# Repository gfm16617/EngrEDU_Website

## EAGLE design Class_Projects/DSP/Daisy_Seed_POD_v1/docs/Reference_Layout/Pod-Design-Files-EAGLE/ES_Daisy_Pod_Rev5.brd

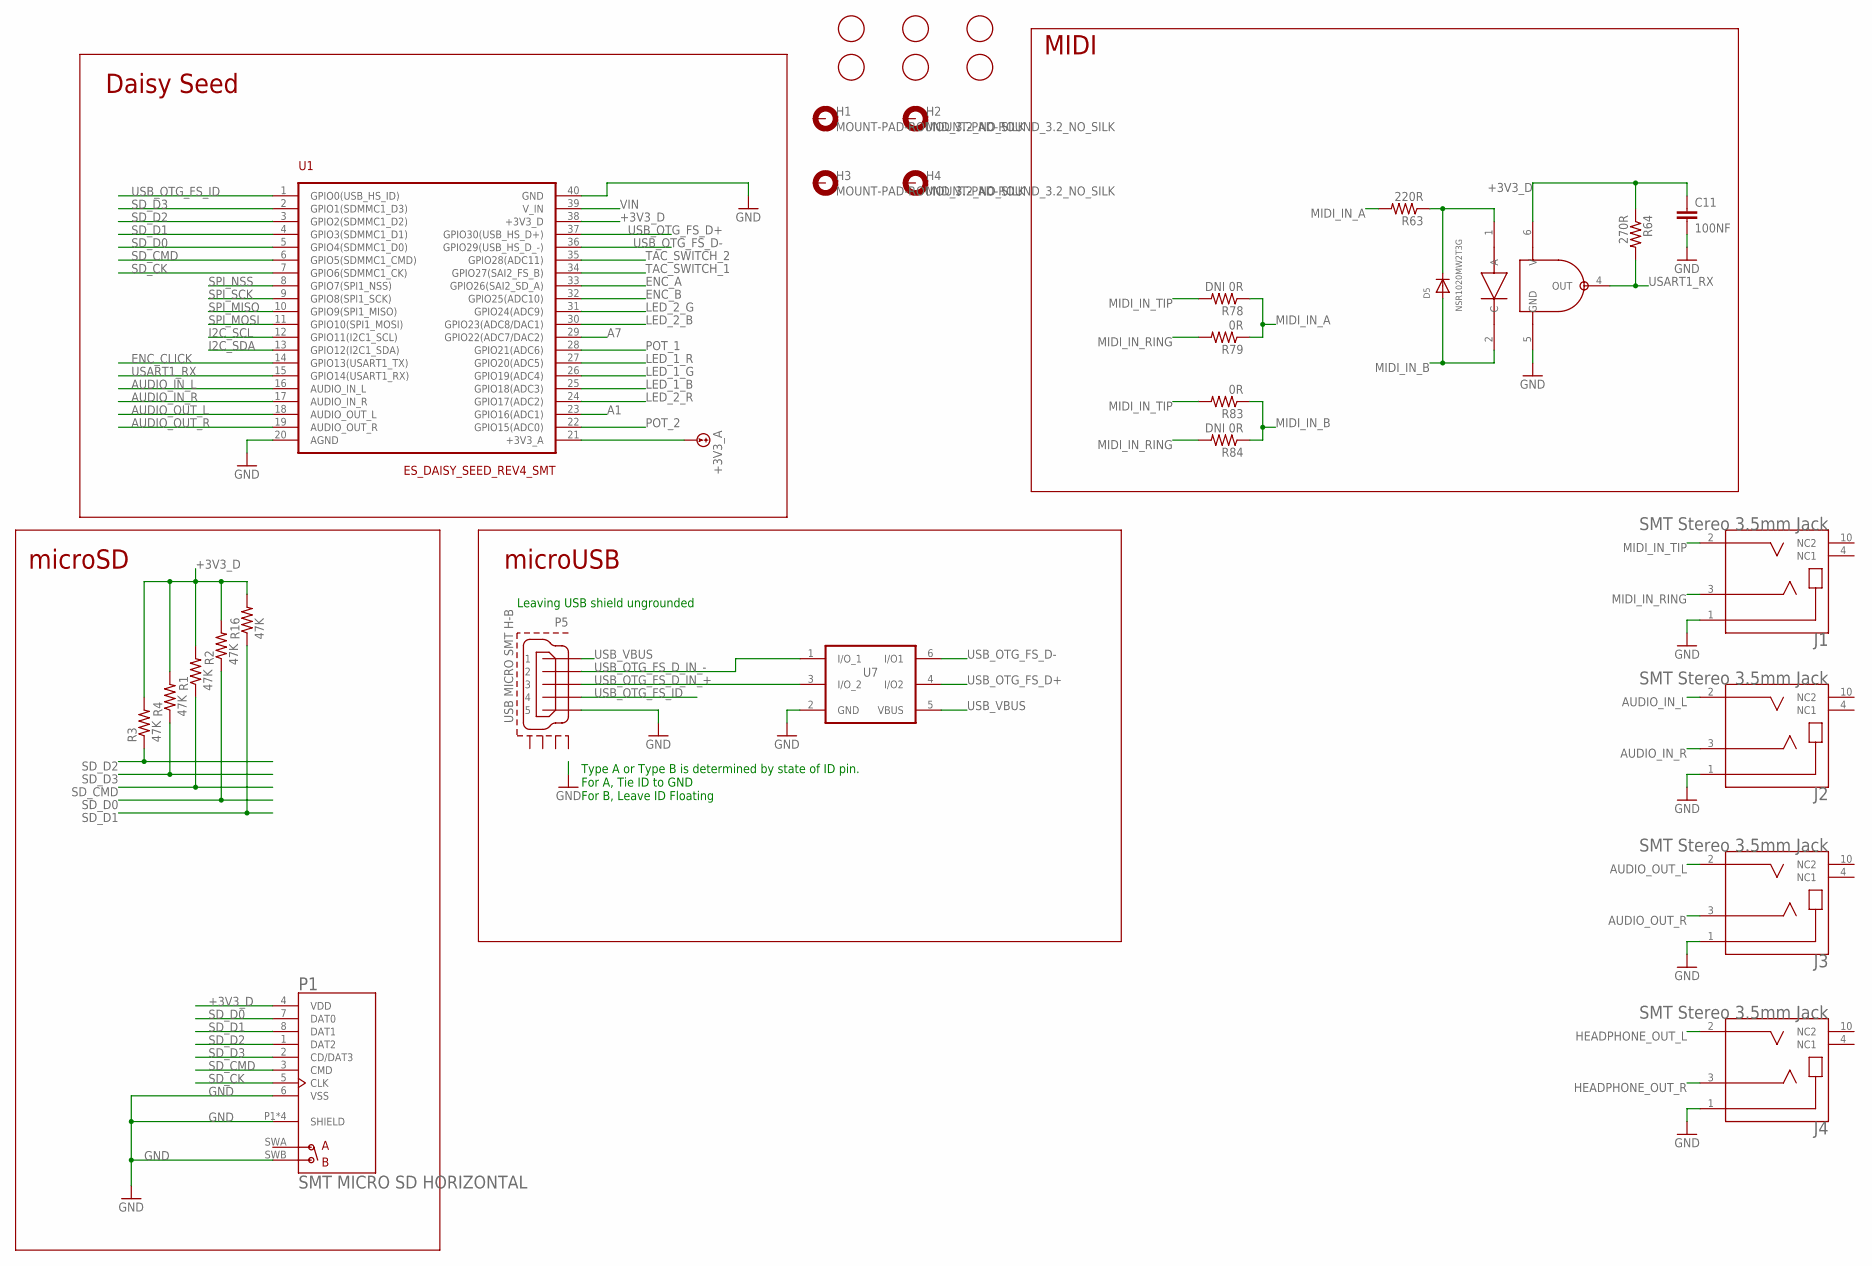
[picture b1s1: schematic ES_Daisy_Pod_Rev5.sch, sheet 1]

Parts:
C11: 100NF; C0402
D5: NSR1020MW2T3G; SOD-323F
FD1, FD2, FD3, FD4, FD5, FD6: FIDUCIAL; FIDUCIAL_1MM
H1, H2, H3, H4: MOUNT-PAD-ROUND_3.2_NO_SILK; 32-PAD_NO_SILK
J1, J2, J3, J4: SMT Stereo 3.5mm Jack; CUI_SJ2-35863B1-SMT-TR
P1: SMT MICRO SD HORIZONTAL; HRS_DM3AT-SF-PEJM5
P5: USB MICRO SMT H-B; 47589-0001_CUT2
R1, R2, R3, R4, R16: 47K; R0603
R63: 220R; R0603
R64: 270R; R0603
R78, R84: DNI 0R; R0603
R79, R83: 0R; R0603
U1: ES_DAISY_SEED_REV4_SMT; ES_DAISY_SEED_SMT
U7: USBLC6 TVS SOT-23-6; SOT-23-6L
U15: H11L1SR2M; DIL06_GULLWING

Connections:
+3V3_A: U1.21 (+3V3_A); also elsewhere on the board
+3V3_D: C11.1, P1.4 (VDD), R1.2, R2.2, R3.2, R4.2, R16.2, R64.1, U1.38 (+3V3_D), U15.6 (V); also elsewhere on the board
A1: U1.23 (GPIO16(ADC1)); also elsewhere on the board
A7: U1.29 (GPIO22(ADC7/DAC2)); also elsewhere on the board
AUDIO_IN_L: J2.2 (TIP), U1.16 (AUDIO_IN_L)
AUDIO_IN_R: J2.3 (RING), U1.17 (AUDIO_IN_R)
AUDIO_OUT_L: J3.2 (TIP), U1.18 (AUDIO_OUT_L); also elsewhere on the board
AUDIO_OUT_R: J3.3 (RING), U1.19 (AUDIO_OUT_R); also elsewhere on the board
ENC_A: U1.33 (GPIO26(SAI2_SD_A)); also elsewhere on the board
ENC_B: U1.32 (GPIO25(ADC10)); also elsewhere on the board
ENC_CLICK: U1.14 (GPIO13(USART1_TX)); also elsewhere on the board
GND: C11.2, J1.1 (SLEEVE), J2.1 (SLEEVE), J3.1 (SLEEVE), J4.1 (SLEEVE), P1.6 (VSS), P1.P1 (SHIELD), P1.P2 (SHIELD), P1.P3 (SHIELD), P1.P4 (SHIELD), P1.SWB (B), P5.5, U1.20 (AGND), U1.40 (GND), U7.2 (GND), U15.5 (GND); also elsewhere on the board
HEADPHONE_OUT_L: J4.2 (TIP); also elsewhere on the board
HEADPHONE_OUT_R: J4.3 (RING); also elsewhere on the board
I2C_SCL: U1.12 (GPIO11(I2C1_SCL)); also elsewhere on the board
I2C_SDA: U1.13 (GPIO12(I2C1_SDA)); also elsewhere on the board
LED_1_B: U1.25 (GPIO18(ADC3)); also elsewhere on the board
LED_1_G: U1.26 (GPIO19(ADC4)); also elsewhere on the board
LED_1_R: U1.27 (GPIO20(ADC5)); also elsewhere on the board
LED_2_B: U1.30 (GPIO23(ADC8/DAC1)); also elsewhere on the board
LED_2_G: U1.31 (GPIO24(ADC9)); also elsewhere on the board
LED_2_R: U1.24 (GPIO17(ADC2)); also elsewhere on the board
MIDI_IN_A: R63.2, R78.1, R79.1
MIDI_IN_B: D5.A, R83.1, R84.1, U15.2 (C)
MIDI_IN_RING: J1.3 (RING), R79.2, R84.2
MIDI_IN_TIP: J1.2 (TIP), R78.2, R83.2
unnamed: D5.C, R63.1, U15.1 (A)
POT_1: U1.28 (GPIO21(ADC6)); also elsewhere on the board
POT_2: U1.22 (GPIO15(ADC0)); also elsewhere on the board
SD_CK: P1.5 (CLK), U1.7 (GPIO6(SDMMC1_CK))
SD_CMD: P1.3 (CMD), R1.1, U1.6 (GPIO5(SDMMC1_CMD))
SD_D0: P1.7 (DAT0), R2.1, U1.5 (GPIO4(SDMMC1_D0))
SD_D1: P1.8 (DAT1), R16.1, U1.4 (GPIO3(SDMMC1_D1))
SD_D2: P1.1 (DAT2), R3.1, U1.3 (GPIO2(SDMMC1_D2))
SD_D3: P1.2 (CD/DAT3), R4.1, U1.2 (GPIO1(SDMMC1_D3))
SPI_MISO: U1.10 (GPIO9(SPI1_MISO)); also elsewhere on the board
SPI_MOSI: U1.11 (GPIO10(SPI1_MOSI)); also elsewhere on the board
SPI_NSS: U1.8 (GPIO7(SPI1_NSS)); also elsewhere on the board
SPI_SCK: U1.9 (GPIO8(SPI1_SCK)); also elsewhere on the board
TAC_SWITCH_1: U1.34 (GPIO27(SAI2_FS_B)); also elsewhere on the board
TAC_SWITCH_2: U1.35 (GPIO28(ADC11)); also elsewhere on the board
USART1_RX: R64.2, U1.15 (GPIO14(USART1_RX)), U15.4 (OUT)
USB_OTG_FS_D+: U1.37 (GPIO30(USB_HS_D+)), U7.4 (I/O2)
USB_OTG_FS_D-: U1.36 (GPIO29(USB_HS_D_-)), U7.6 (I/O1)
USB_OTG_FS_D_IN_+: P5.3, U7.3 (I/O_2)
USB_OTG_FS_D_IN_-: P5.2, U7.1 (I/O_1)
USB_OTG_FS_ID: P5.4, U1.1 (GPIO0(USB_HS_ID))
USB_VBUS: P5.1, U7.5 (VBUS)
VIN: U1.39 (V_IN); also elsewhere on the board

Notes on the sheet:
Daisy Seed
microSD
Type A or Type B is determined by state of ID pin. For A, Tie ID to GND For B, Leave ID Floating
Leaving USB shield ungrounded
microUSB
MIDI

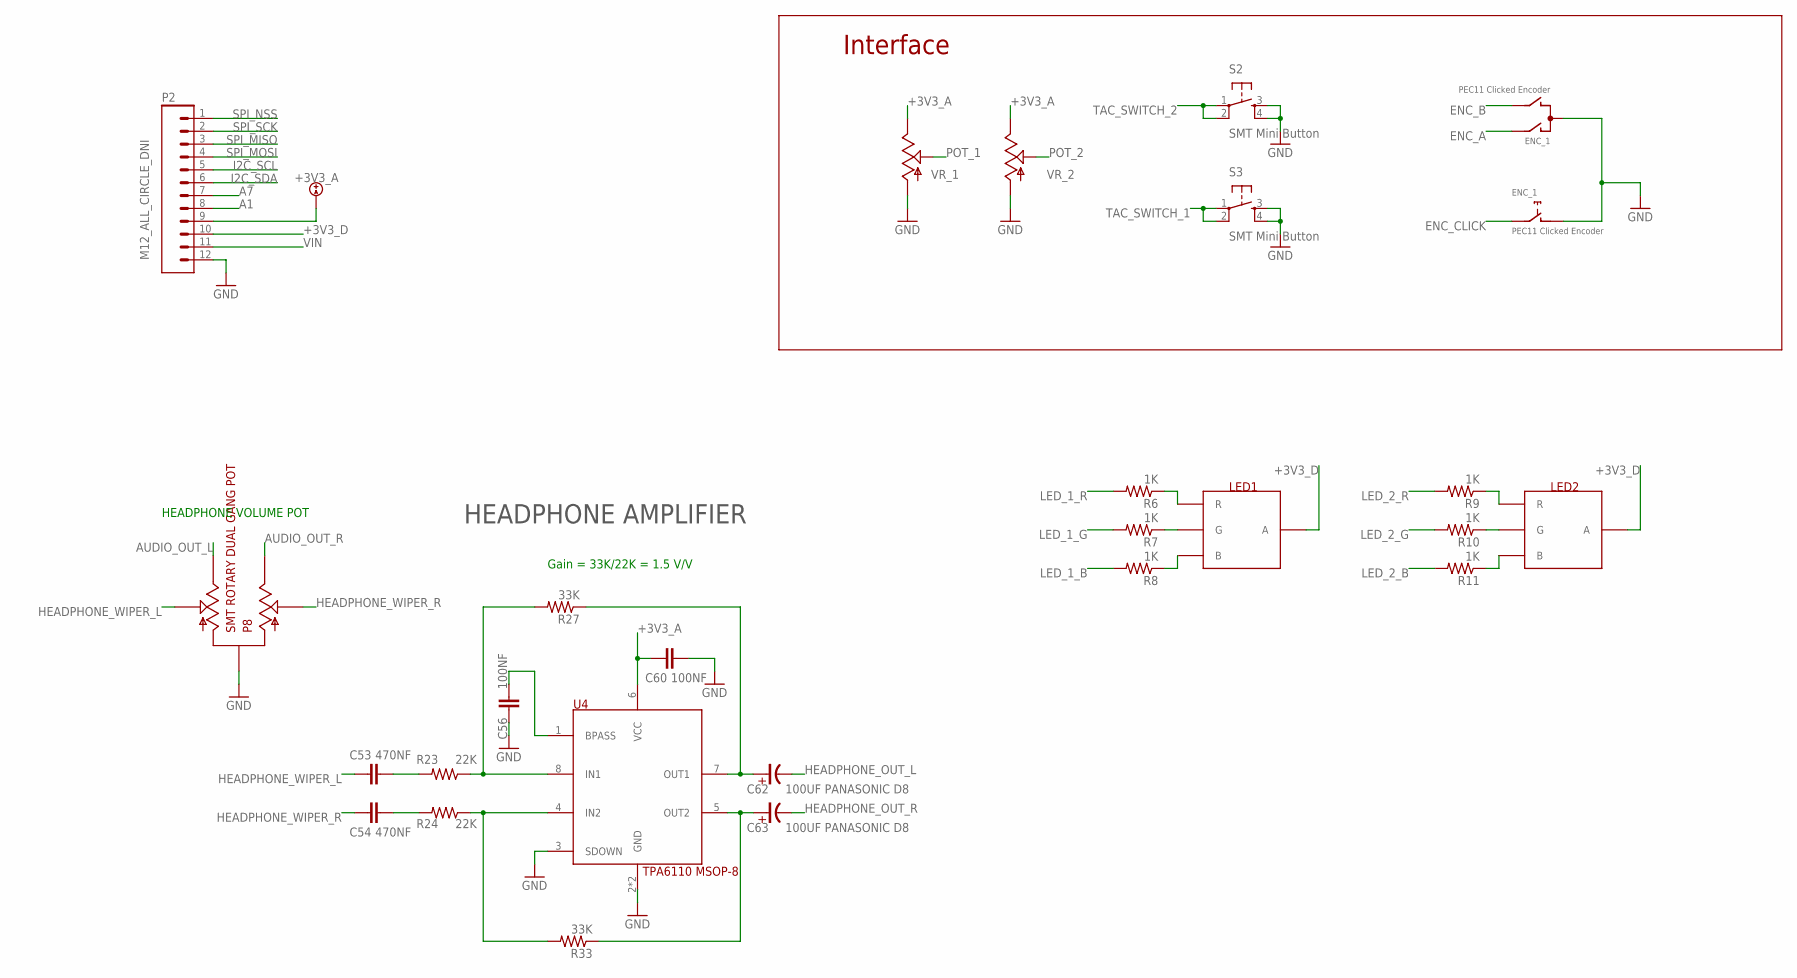
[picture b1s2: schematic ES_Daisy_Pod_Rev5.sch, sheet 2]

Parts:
C53, C54: 470NF; C0603
C56, C60: 100NF; C0402
C62, C63: 100UF PANASONIC D8; PANASONIC_D
ENC_1: PEC11 Clicked Encoder; VH1-147
LED1, LED2: RGB LED SMT PLCC4; P-LCC-4-3
P2: M12_ALL_CIRCLE_DNI; 1X12_NO_SILK_ALL_CIRCLE
P8: SMT ROTARY DUAL GANG POT; RK10J12R0A0B
R6, R7, R8, R9, R10, R11: 1K; R0402
R23, R24: 22K; R0603
R27, R33: 33K; R0603
S2, S3: SMT Mini Button; TL3301SPF160QJ
U4: TPA6110 MSOP-8; MSOP_8_PWRPAD
VR_1, VR_2: P-10K-B-R-PIP; 9MM_SNAP-IN_POT_SILK_PIP

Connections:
+3V3_A: C60.2, P2.9, U4.6 (VCC), VR_1.3, VR_2.3; also elsewhere on the board
+3V3_D: LED1.2 (A), LED2.2 (A), P2.10; also elsewhere on the board
A1: P2.8; also elsewhere on the board
A7: P2.7; also elsewhere on the board
AUDIO_OUT_L: P8.P$5; also elsewhere on the board
AUDIO_OUT_R: P8.P$4; also elsewhere on the board
ENC_A: ENC_1.A; also elsewhere on the board
ENC_B: ENC_1.B; also elsewhere on the board
ENC_CLICK: ENC_1.E (2); also elsewhere on the board
GND: C56.1, C60.1, ENC_1.C, ENC_1.D (1), P2.12, P8.P$1, S2.3, S2.4, S3.3, S3.4, U4.2 (GND), U4.3 (SDOWN), U4.9 (GND), VR_1.1, VR_2.1; also elsewhere on the board
HEADPHONE_OUT_L: C62.- (NEG); also elsewhere on the board
HEADPHONE_OUT_R: C63.- (NEG); also elsewhere on the board
HEADPHONE_WIPER_L: C53.1, P8.P$2
HEADPHONE_WIPER_R: C54.1, P8.P$3
I2C_SCL: P2.5; also elsewhere on the board
I2C_SDA: P2.6; also elsewhere on the board
LED_1_B: R8.2; also elsewhere on the board
LED_1_G: R7.2; also elsewhere on the board
LED_1_R: R6.2; also elsewhere on the board
LED_2_B: R11.2; also elsewhere on the board
LED_2_G: R10.2; also elsewhere on the board
LED_2_R: R9.2; also elsewhere on the board
unnamed: LED1.1 (R), R6.1
unnamed: LED1.4 (G), R7.1
unnamed: LED1.3 (B), R8.1
unnamed: LED2.1 (R), R9.1
unnamed: LED2.4 (G), R10.1
unnamed: LED2.3 (B), R11.1
unnamed: C54.2, R24.2
unnamed: R23.1, R27.2, U4.8 (IN1)
unnamed: R24.1, R33.2, U4.4 (IN2)
unnamed: C53.2, R23.2
unnamed: C56.2, U4.1 (BPASS)
unnamed: C62.+ (POS), R27.1, U4.7 (OUT1)
unnamed: C63.+ (POS), R33.1, U4.5 (OUT2)
POT_1: VR_1.2; also elsewhere on the board
POT_2: VR_2.2; also elsewhere on the board
SPI_MISO: P2.3; also elsewhere on the board
SPI_MOSI: P2.4; also elsewhere on the board
SPI_NSS: P2.1; also elsewhere on the board
SPI_SCK: P2.2; also elsewhere on the board
TAC_SWITCH_1: S3.1, S3.2; also elsewhere on the board
TAC_SWITCH_2: S2.1, S2.2; also elsewhere on the board
VIN: P2.11; also elsewhere on the board

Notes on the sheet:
Interface
HEADPHONE VOLUME POT
HEADPHONE AMPLIFIER
Gain = 33K/22K = 1.5 V/V

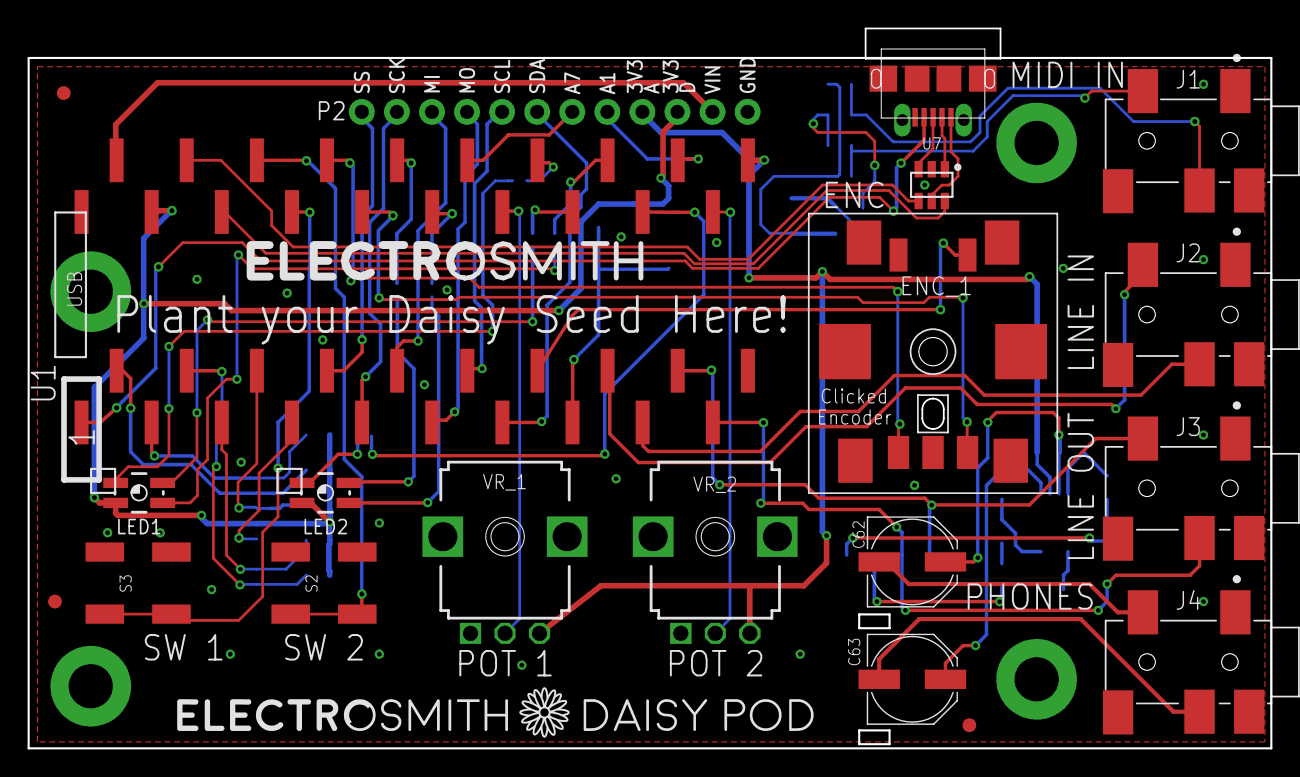
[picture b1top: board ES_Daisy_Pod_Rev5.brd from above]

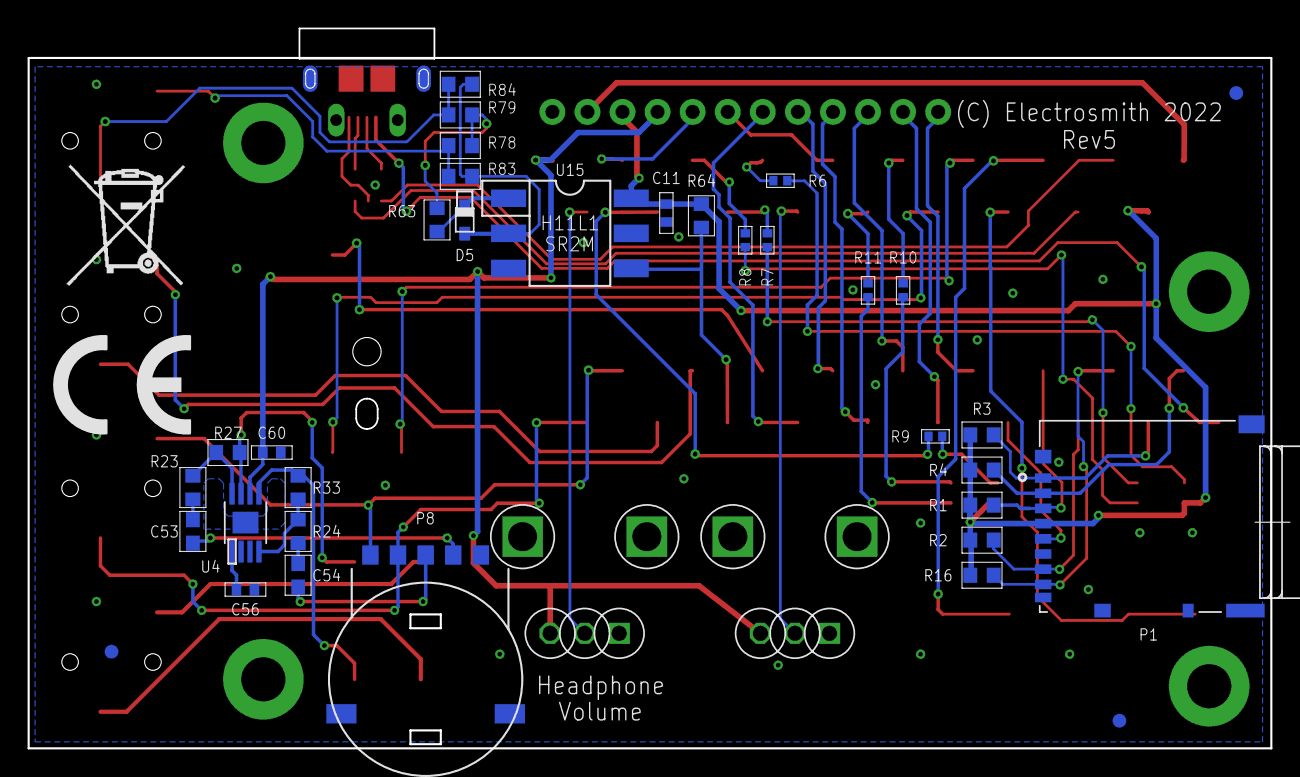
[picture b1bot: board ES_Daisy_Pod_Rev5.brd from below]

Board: 2 copper layers, 90.0 x 52.1 mm, 62 parts (36 on the bottom side), 64 nets.

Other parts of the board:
U$2: TONNE_9X13MM
U$3: CE_10X7.3MM
U$4: DAISY_POD_BRANDING_2
U$7: ES_TEXT_3X30MM

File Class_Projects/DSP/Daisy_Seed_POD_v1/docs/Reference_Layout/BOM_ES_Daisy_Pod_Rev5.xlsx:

Qty | IPN | MPN | Manufacturer | Designators | Vendor Link
5 | 47K R0603 | RC0603FR-0747KL | Yageo | R3 R4 R1 R2 R16 | Mouser
1 | USB MICRO SMT H-B | 47589-0001 | Molex | P5 | Mouser
2 | SMT Mini Button | TL3301SPF160QJ | E-Switch | S2 S3 | Mouser
1 | 220R R0603 | RC0603FR-07220RL | Yageo | R63 | Mouser
1 | 270R R0603 | CRCW0603270RFKEAC | Vishay | R64 | Mouser
3 | 100NF C0402 | CC0402KPX5R8BB104 | Yageo | C11 C56 C60 | Mouser
2 | 470NF C0603 | CL10B474KA8NFNC | Samsung | C53 C54 | Mouser
2 | 22K R0603 | RC0603FR-0722KL | Yageo | R23 R24 | Mouser
2 | 33K R0603 | RC0603FR-1333KL | Yageo | R27 R33 | Mouser
2 | RGB LED SMT PLCC4 | CLVBA-FKA-CAEDH8BBB7a363 | Cree | LED1 LED2 | Mouser
6 | 1K R0402 | RC0402FR-131KL | Yageo | R6 R7 R8 R9 R10 R11 | Mouser
4 | 0R R0603 | AC0603FR-070RL | Yageo | R79 R83 R78 R84 | Mouser
1 | USBLC6 TVS SOT-23-6 | USBLC6-2SC6TR | ST Micro | U7 | DigiKey
1 | NSR1020MW2T3G | NSR1020MW2T3G | On Semi | D5 | Mouser
1 | OPTO ISOLATOR | H11L1SR2M | On Semi | U15 | Mouser
1 | TPA6110 MSOP-8 | TPA6110A2DGNR | Texas Instruments | U4 | Mouser
2 | 100UF PANASONIC D8 | EMVE350ARA101MF80G | Chemi-Co | C63 C62 | Mouser
1 | EC11 Detented SMT Encoder | PEC11J-9220F-H0015 | Bourns | ENC_1 | Mouser
4 | SMT-JACK-S-H-3.5 | SJ2-35863B1-SMT-TR | CUI | J2 J3 J4 J1 | Mouser
1 | SMT MICRO SD HORIZONTAL | DM3AT-SF-PEJM5 | Hirose | P1 | Mouser
2 | P-10K-B-R Pointer | R0904N-B10K,L-25KQ/LWS | Song Huei | VR_1 VR_2 | Thonk
1 | 1X20 FEMALE SMT 2.54MM VERTICAL | SSM-120-L-SV | Samtec | U1 | Mouser
1 | SMT ROTARY DUAL GANG POT | RK10J12R0A0B | Alps | P8 | Mouser

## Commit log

2022-05-20 LTSpice Variable Parameter
2022-05-20 Example 1 .op simulation
2022-05-20 Example 1 simulation transient with multiple parameters
2022-05-21 Variable Parameter Maximum Power Transfer
2022-05-21 Example 2
2022-05-21 Variable Resistor and Potentiometer Files
2022-05-21 Potentiometer Example
2022-05-21 External Libraries
2022-05-21 Example 1 DC
2022-05-22 Dependent Sources Examples
2022-05-22 Depende Sources Remove Files
2022-05-22 New Dependent Source Files
2022-05-22 New Files added
2022-05-22 Switches Examples
2022-05-22 RLC Added
2022-05-22 example deleted
2022-05-22 new example 2 file
2022-05-26 Okika LP Test
2022-05-27 File updated
2022-05-27 New okika file 16Mhz
2022-05-27 Pi ahf file
2022-05-27 Option 1 FPAA code
2022-05-27 FPAA Arduino Uno Project
2022-05-27 FPAA Dynamic Reconfiguration
2022-05-27 FPAA Starter Board PCB
2022-06-08 Phasor Circuits
2022-06-08 Fourier Series Articles
2022-11-14 FFT Article
2022-11-14 Another guitar distortion pedal
2022-11-21 gnuradio intro examples
2022-11-21 NI DAQ fist example
2022-11-29 gnuradio projects fundamentals
2022-11-29 gnuradio freq domain real vs complex
2022-11-29 gnuradio freq linearity
2022-11-29 gnuradio convolution
2022-11-30 gnuradio iq transmitter
2022-11-30 folder removed
2022-11-30 gnuradio constellations
2022-11-30 gnuradio am modulation
2022-11-30 gnuradio am voice example
2022-11-30 gnuradio am ssb
2022-11-30 product demodulator fix
2022-12-02 gnuradio frequency direction
2022-12-02 gnuradio fm modulation
2022-12-05 ook modulation (ask)
2022-12-05 m-ary ask modulation
2022-12-06 fsk modulation examples
2022-12-07 bfsk modulation
2022-12-08 PSK modulation examples
2022-12-08 new qpsk module
2022-12-08 rrc_pulse_shapes
2022-12-09 BPSK and QPSK gnuradio examples
2022-12-09 QAM gnuradio flowgraph
2022-12-09 ni daq info code
2022-12-09 remove old folder
2023-02-24 ni daq ai single demand
2023-02-24 remove file
2023-02-24 ni daq single demand matplotlib and pyqtgraph
2023-02-27 ni daq on demand gui
2023-03-05 ni daq single finite
2023-03-06 ni single ai continuous
2023-03-07 simple FM Radio
2023-03-09 version 2
2023-03-23 PCB Tutorial Board March 2023
2023-03-23 arduino code
2023-03-23 remove folder
2023-03-23 PCB Tutorial Kitchen Timer (March 2023)
2023-03-23 gerber zip file
2023-03-26 new code
2023-03-26 new files
2023-04-05 new version of the code with comments according to mutex standards
2023-04-05 Phase B
2023-04-06 alirugdlfghdflkgjdahgka
2023-04-06 gdsagdsa
2023-04-06 Clock version 2.2
2023-04-23 ATMEGA dev board files
2023-06-07 arduino code timers CTC
2023-06-07 new timer version
2023-06-08 timer 2 ctc example
2023-07-22 new documents about visa and scpi
2023-07-22 python code examples
2023-07-31 python code example that shows the different ways to acquire data from the NI DAQ
2023-08-01 bad code removed
2023-08-01 MCP4251 simple test
2023-09-26 electric vlsi icon article
2024-02-08 up1 class arduino code for shield
2024-02-08 comment a line of code
2024-02-08 removed extra file
2024-05-26 final project PCB schedule for embedded systems class
2024-05-26 DDS Shield PCB Design Files
2024-05-26 pcb components
2024-05-26 unzip these components here
2024-05-26 stm32f dds code
2024-05-26 some code for now
2024-05-26 dds stm32f405 pcb design
2024-05-26 components
2024-05-26 unzip here
2024-05-28 stm32cubeide project
2024-05-28 main.c deleted
2024-05-31 new board version
2024-06-01 schematics fixed
2024-06-07 UART FTDI PCB KiCad Project
2024-06-08 FTDI 3D Support
2024-06-26 ECG KiCad projects
2024-06-27 charge pump kicad project
2024-06-30 RP2040
2024-07-16 fixes
2024-09-06 RP2040 Kicad 8.0 Project
2024-10-30 Project 15 - EngrEDU
2024-11-23 codde for the STM32C011J
2024-11-24 I2C resistor addded to the PCB
2024-11-24 STM32C011J IMU Test
2024-11-25 ADS8689 PCB Board
2024-11-25 ADS8689 PCB and Arduino Code
2024-11-25 removed initial project ADS8689
2024-12-22 STM32F303 Teensy Shape
2024-12-22 STM32F303 ST32CubeIDE Project
2025-02-02 Project 18
2025-02-13 old version
2025-02-13 new version
2025-05-21 Brush EBoot Version 1
2025-07-07 test run
2025-09-06 fgpa articles first file
2025-09-08 blinkled Quartus Project
2025-09-23 ultrasonic sensor code
2025-10-19 example
2025-10-19 kicad project
2025-10-19 removed
2025-10-19 board
2025-10-19 audio board test
2025-10-19 board test
2025-12-04 levitation project test
2025-12-04 wrl board
2026-01-04 PCbCupid Example
2026-01-04 folder deleted
2026-02-14 microprocessors 1 2026 project
2026-02-15 gerber
2026-03-11 audio mixer done in 2022 for circuits 1
2026-03-11 audio mixer duo for circuits 1 class 2022
2026-03-11 firmware code to interact with AD2 serial
2026-03-15 OTC231 firmware code to program the FPAA using AD2 software
2026-03-16 code for state driven example with ESP32 and OTC231
2026-03-17 algorithm method example for ESP32
2026-03-17 OTC231 algorithm example
2026-03-17 okika articles test with github and wordpress
2026-03-17 mkdocs build
2026-03-18 okika articles removed
2026-03-20 ESP32 webserver example
2026-04-03 2026 stm32 blink project
2026-04-03 python for engineers installation files
2026-04-16 test
2026-04-16 deleted
2026-04-17 HC-SR04 project solution
2026-04-19 eurorack module done in 2020, documentation revised
2026-05-01 new projects added to the repository. 2026 Embedded System Project 2026 Daisy Seed POD Board
2026-05-22 added new wrl files into daisy pod
2026-06-01 3Wheel code and CAD files added
2026-06-01 stm32cube code uploaded for the 3wheel version
2026-06-14 added files for Okika standalone single AN231 chip with protoboard
2026-06-21 ESP32 and FPAA Analoguino
2026-06-21 firmware code uploaded
2026-06-24 add random python file
2026-06-25 OTC code added
2026-06-25 new OTC2312 bypass
2026-06-29 OTC2312 State Driven example
2026-06-30 2026_ESP32_FPAA_v3 added with Analog pins on ESP32 fixed
2026-06-30 Delete Okika/2026_ESP32_FPAA_v2 directory
    no longer needed

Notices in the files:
parts and their libraries:
Electrosmith-Connectors: (C) 2014 Tomasz Boleslaw CEDRO, cederom@tlen.pl, http://www.tomek.cedro.info.
